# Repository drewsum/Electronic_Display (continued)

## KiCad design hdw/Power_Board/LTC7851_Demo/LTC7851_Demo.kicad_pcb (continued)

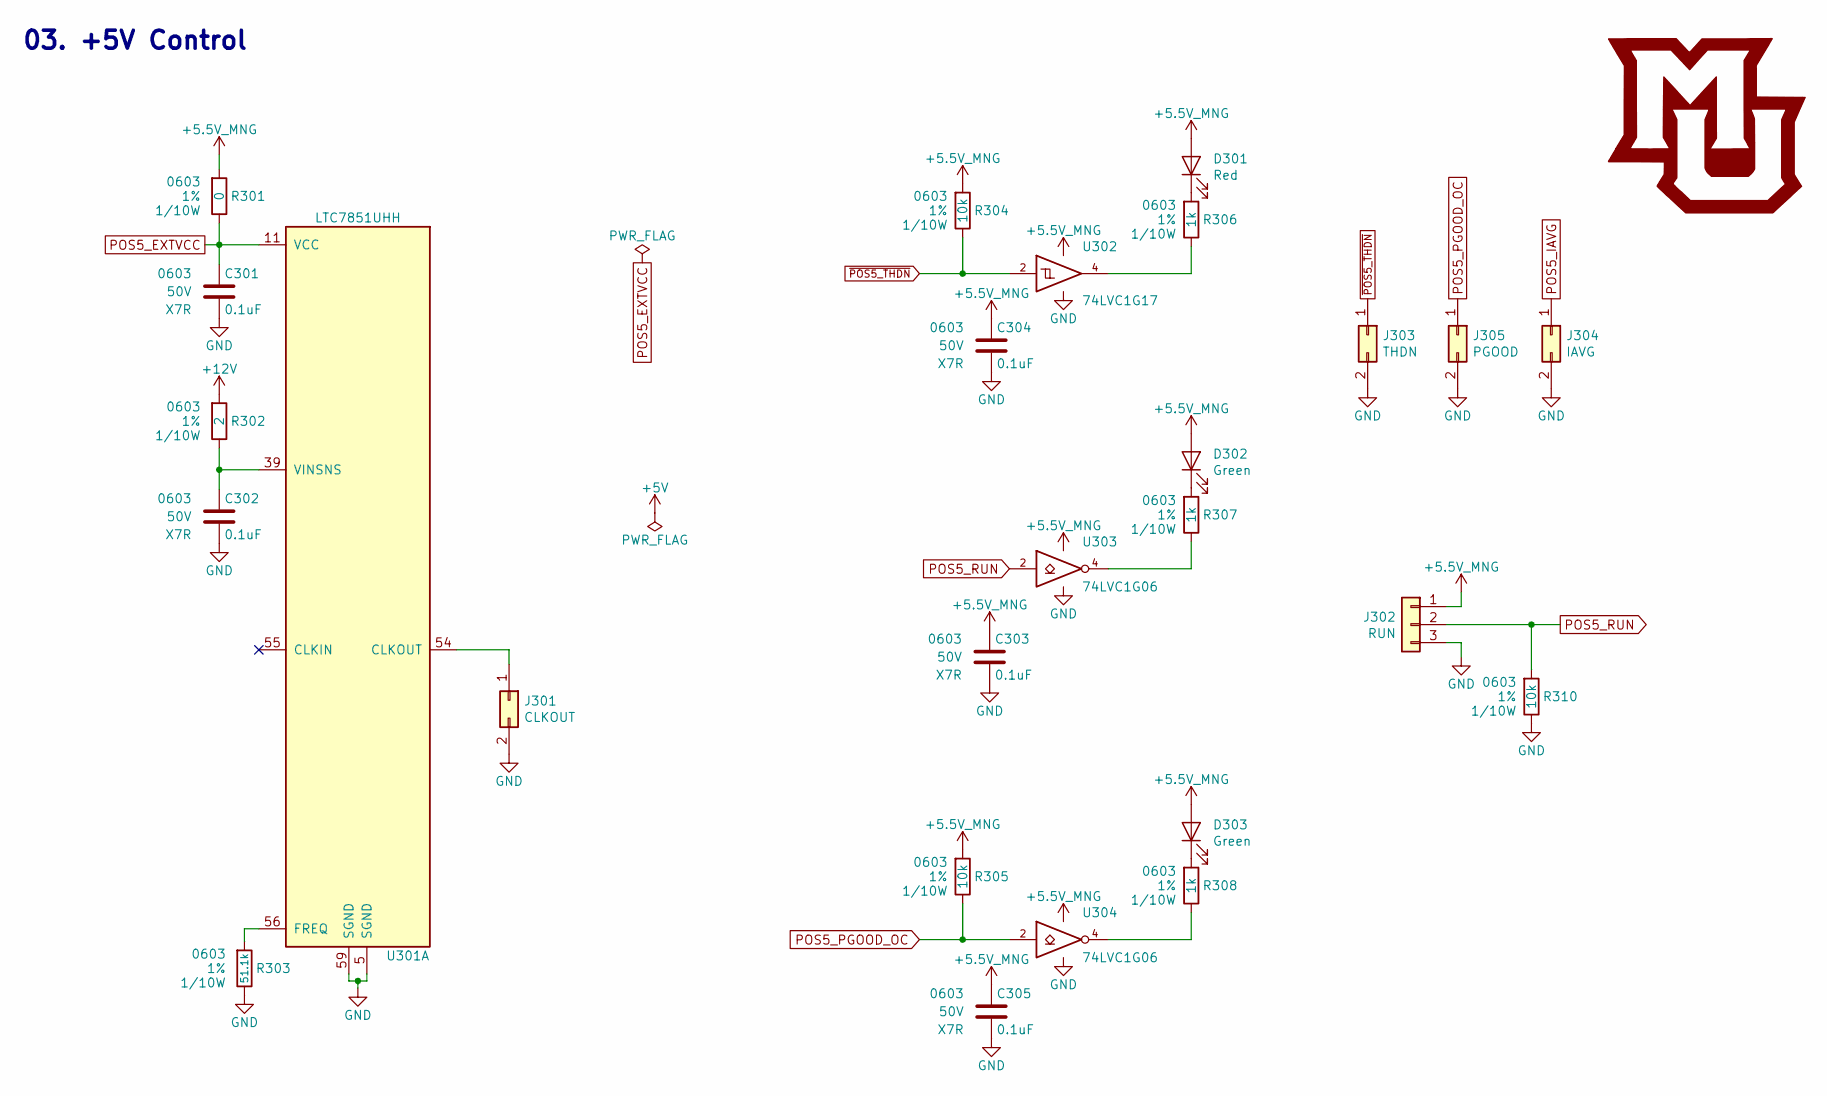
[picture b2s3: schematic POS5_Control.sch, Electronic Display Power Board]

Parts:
C301, C302, C303, C304, C305: 0.1uF; C_0603; Voltage 50V; Digi-Key PN 490-4779-1-ND
D301: Red; LED_0603; Digi-Key PN 160-1447-1-ND
D302, D303: Green; LED_0603; Digi-Key PN 160-1446-1-ND
J301: CLKOUT; Pin_Header_Straight_1x02_Pitch2.54mm
J302: RUN; Pin_Header_Straight_1x03_Pitch2.54mm
J303: THDN; Pin_Header_Straight_1x02_Pitch2.54mm
J304: IAVG; Pin_Header_Straight_1x02_Pitch2.54mm
J305: PGOOD; Pin_Header_Straight_1x02_Pitch2.54mm
R301: 0; R_0603; Tolerance 1%; Digi-Key PN 311-0.0GRCT-ND
R302: 2; R_0603; Tolerance 1%; Digi-Key PN RMCF0603FT2R00CT-ND
R303: 51.1k; R_0603; Tolerance 1%; Digi-Key PN P51.1KHCT-ND
R304, R305, R310: 10k; R_0603; Tolerance 1%; Digi-Key PN RHM10KADCT-ND
R306, R307, R308: 1k; R_0603; Tolerance 1%; Digi-Key PN RHM1.0KDCT-ND
U301: LTC7851UHH; QFN-58-1EP_9x5mm_Pitch0.4mm; Digi-Key PN LTC7851IUHH#PBF-ND
U302: 74LVC1G17; SOT-353_SC-70-5; Digi-Key PN 296-11934-1-ND
U303, U304: 74LVC1G06; SOT-353_SC-70-5; Digi-Key PN 296-8484-1-ND

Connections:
+5.5V_MNG: C303.1, C304.1, C305.1, D301.2 (A), D302.2 (A), D303.2 (A), J302.1, R301.1, R304.1, R305.1, U302.5 (VCC), U303.5 (VCC), U304.5 (VCC); also elsewhere on the board
+12V: R302.1; also elsewhere on the board
GND: C301.2, C302.2, C303.2, C304.2, C305.2, J301.2, J302.3, J303.2, J304.2, J305.2, R303.2, R310.2, U301.5 (SGND), U301.59 (SGND), U302.3 (GND), U303.3 (GND), U304.3 (GND); also elsewhere on the board
unnamed: C302.1, R302.2, U301.39 (VINSNS)
unnamed: D301.1 (K), R306.1
unnamed: D302.1 (K), R307.1
unnamed: D303.1 (K), R308.1
unnamed: J301.1, U301.54 (CLKOUT)
unnamed: R303.1, U301.56 (FREQ)
unnamed: R306.2, U302.4
unnamed: R307.2, U303.4
unnamed: R308.2, U304.4
POS5_EXTVCC: C301.1, R301.2, U301.11 (VCC); also elsewhere on the board
POS5_IAVG: J304.1; also elsewhere on the board
POS5_PGOOD_OC: J305.1, R305.2, U304.2; also elsewhere on the board
POS5_RUN: J302.2, R310.1, U303.2; also elsewhere on the board
~POS5_THDN: J303.1, R304.2, U302.2; also elsewhere on the board

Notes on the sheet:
03. +5V Control

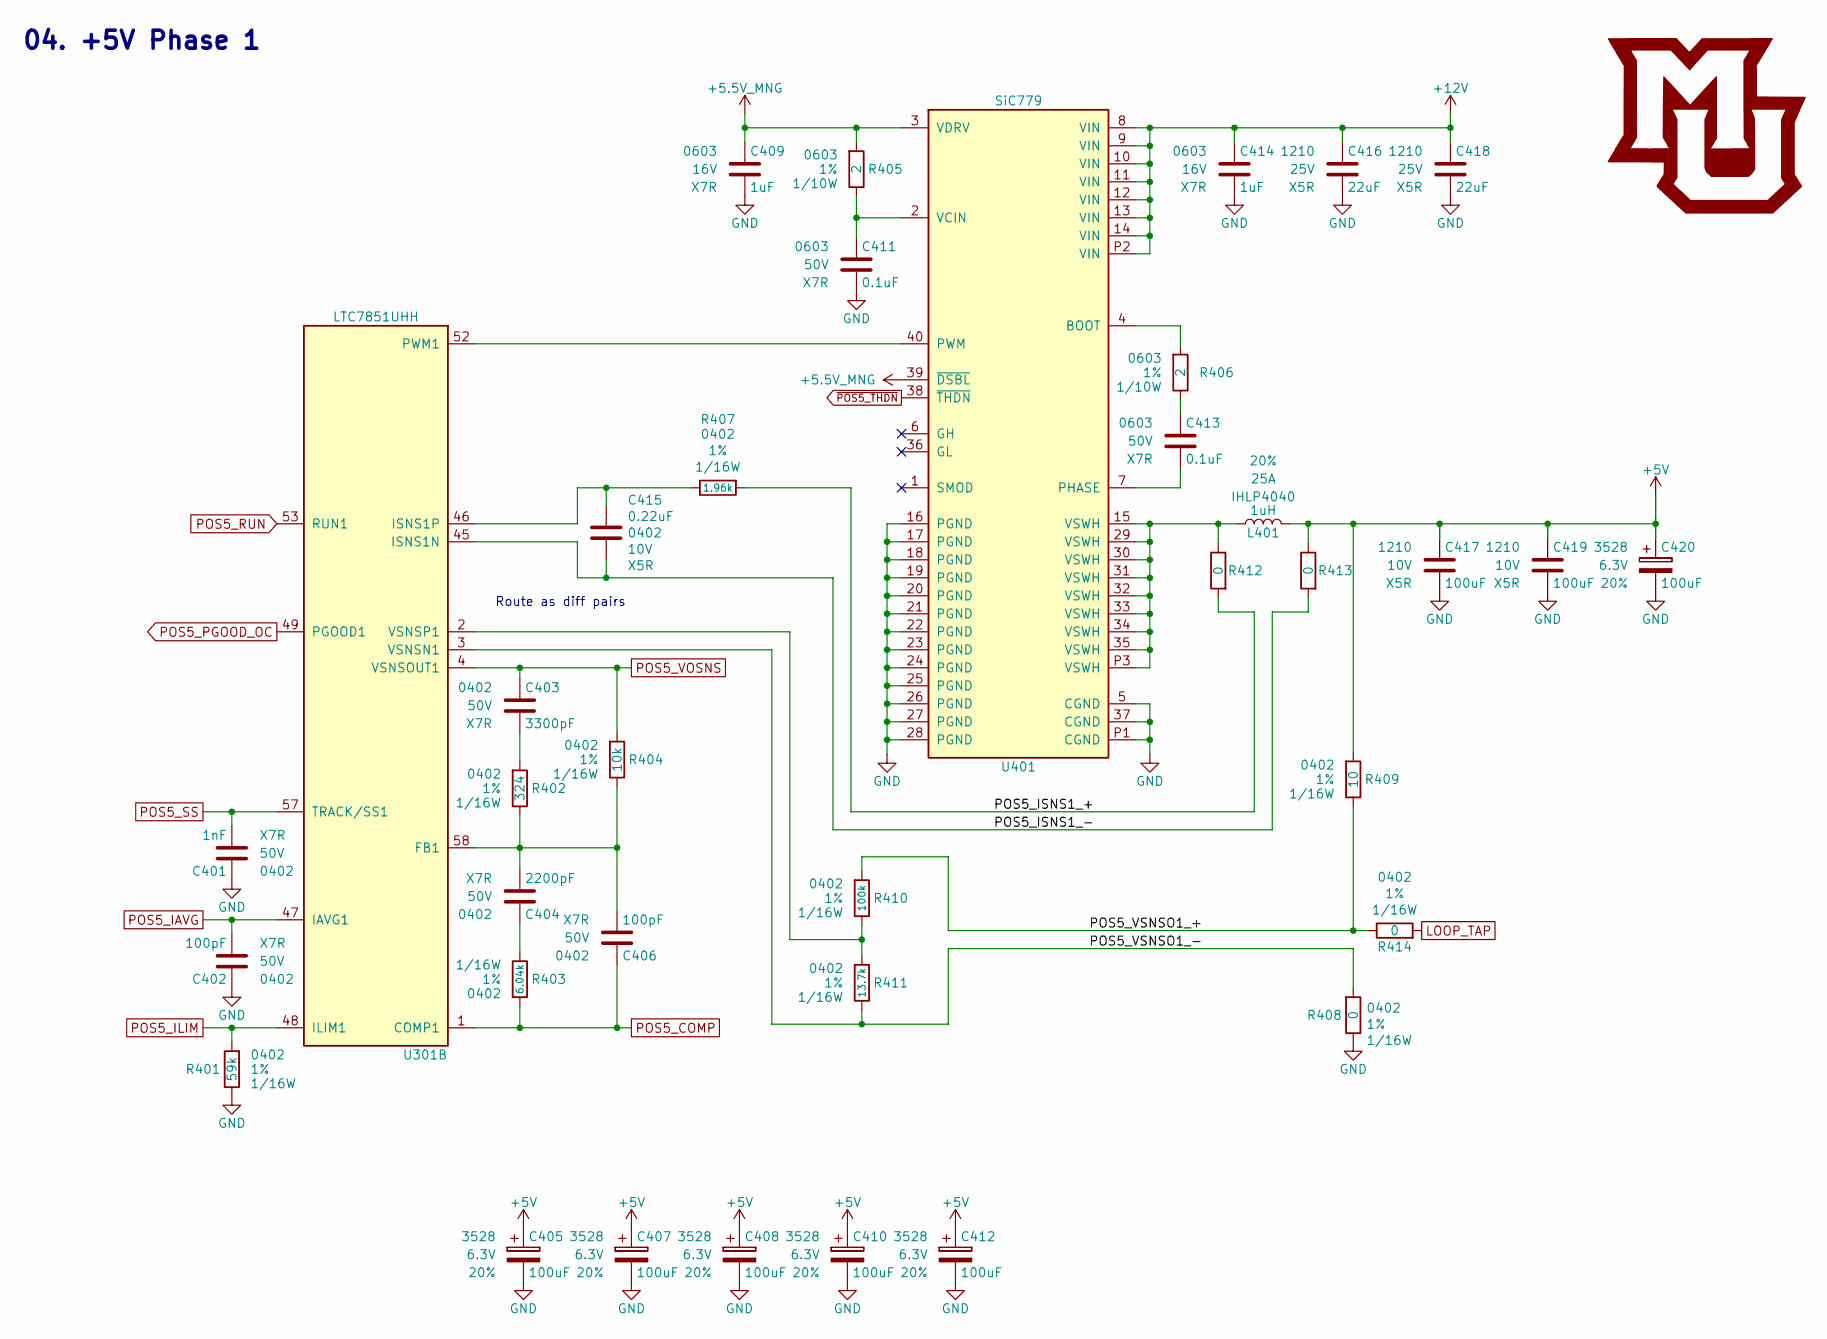
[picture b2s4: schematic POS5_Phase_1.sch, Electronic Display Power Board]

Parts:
C401: 1nF; C_0402; Voltage 50V; Digi-Key PN 311-1080-1-ND
C402, C406: 100pF; C_0402; Voltage 50V; Digi-Key PN 478-1089-1-ND
C403: 3300pF; C_0402; Voltage 50V; Digi-Key PN 478-5132-1-ND
C404: 2200pF; C_0402; Voltage 50V; Digi-Key PN 478-1105-1-ND
C405, C407, C408, C410, C412, C420: 100uF; CP_Tantalum_Case-B_EIA-3528-21_Reflow; Voltage 6.3V; Tolerance 20%; Digi-Key PN 478-9994-1-ND
C409, C414: 1uF; C_0603; Voltage 16V; Digi-Key PN 1276-6524-1-ND
C411, C413: 0.1uF; C_0603; Voltage 50V; Digi-Key PN 490-4779-1-ND
C415: 0.22uF; C_0402; Voltage 10V; Digi-Key PN 1276-1049-1-ND
C416, C418: 22uF; C_1210; Voltage 25V; Digi-Key PN 445-1436-1-ND
C417, C419: 100uF; C_1210; Voltage 10V; Digi-Key PN 587-3432-1-ND
L401: 1uH; L_Vishay_IHLP-4040; Tolerance 20%; Digi-Key PN 541-1306-1-ND
R401: 59k; R_0402; Tolerance 1%; Digi-Key PN P59KDCCT-ND
R402: 324; R_0402; Tolerance 1%; Digi-Key PN YAG3118CT-ND
R403: 6.04k; R_0402; Tolerance 1%; Digi-Key PN RMCF0402FT6K04CT-ND
R404: 10k; R_0402; Tolerance 1%; Digi-Key PN 311-10.0KLRCT-ND
R405, R406: 2; R_0603; Tolerance 1%; Digi-Key PN RMCF0603FT2R00CT-ND
R407: 1.96k; R_0402; Tolerance 1%; Digi-Key PN 311-1.96KLRCT-ND
R408, R412, R413, R414: 0; R_0402; Tolerance 1%; Digi-Key PN RMCF0402ZT0R00CT-ND
R409: 10; R_0402; Tolerance 1%; Digi-Key PN 311-10.0LRCT-ND
R410: 100k; R_0402; Tolerance 1%; Digi-Key PN 311-100KLRCT-ND
R411: 13.7k; R_0402; Tolerance 1%; Digi-Key PN 311-13.7KLRCT-ND
U301: LTC7851UHH; QFN-58-1EP_9x5mm_Pitch0.4mm; Digi-Key PN LTC7851IUHH#PBF-ND
U401: SiC779; MLP66-40_6x6mm_Pitch0.5mm; Digi-Key PN SIC779CD-T1-GE3CT-ND

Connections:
+5.5V_MNG: C409.1, R405.1, U401.3 (VDRV), U401.39 (~DSBL); also elsewhere on the board
+5V: C405.1, C407.1, C408.1, C410.1, C412.1, C417.1, C419.1, C420.1, L401.2, R409.1, R413.2; also elsewhere on the board
+12V: C414.1, C416.1, C418.1, U401.8 (VIN), U401.9 (VIN), U401.10 (VIN), U401.11 (VIN), U401.12 (VIN), U401.13 (VIN), U401.14 (VIN), U401.P2 (VIN); also elsewhere on the board
/POS5 Phase 1/POS5_ISNS1_+: R407.1, R412.1
/POS5 Phase 1/POS5_ISNS1_-: C415.1, R413.1, U301.45 (ISNS1N)
/POS5 Phase 1/POS5_VSNSO1_+: R409.2, R410.1, R414.2
/POS5 Phase 1/POS5_VSNSO1_-: R408.1, R411.2, U301.3 (VSNSN1)
GND: C401.1, C402.1, C405.2, C407.2, C408.2, C409.2, C410.2, C411.2, C412.2, C414.2, C416.2, C417.2, C418.2, C419.2, C420.2, R401.2, R408.2, U401.5 (CGND), U401.16 (PGND), U401.17 (PGND), U401.18 (PGND), U401.19 (PGND), U401.20 (PGND), U401.21 (PGND), U401.22 (PGND), U401.23 (PGND), U401.24 (PGND), U401.25 (PGND), U401.26 (PGND), U401.27 (PGND), U401.28 (PGND), U401.37 (CGND), U401.P1 (CGND); also elsewhere on the board
LOOP_TAP: R414.1; also elsewhere on the board
unnamed: C403.2, R402.1
unnamed: C404.1, R403.2
unnamed: C404.2, C406.2, R402.2, R404.2, U301.58 (FB1)
unnamed: C411.1, R405.2, U401.2 (VCIN)
unnamed: C413.1, R406.2
unnamed: C413.2, U401.7 (PHASE)
unnamed: C415.2, R407.2, U301.46 (ISNS1P)
unnamed: L401.1, R412.2, U401.15 (VSWH), U401.29 (VSWH), U401.30 (VSWH), U401.31 (VSWH), U401.32 (VSWH), U401.33 (VSWH), U401.34 (VSWH), U401.35 (VSWH), U401.P3 (VSWH)
unnamed: R406.1, U401.4 (BOOT)
unnamed: R410.2, R411.1, U301.2 (VSNSP1)
unnamed: U301.52 (PWM1), U401.40 (PWM)
POS5_COMP: C406.1, R403.1, U301.1 (COMP1); also elsewhere on the board
POS5_IAVG: C402.2, U301.47 (IAVG1); also elsewhere on the board
POS5_ILIM: R401.1, U301.48 (ILIM1); also elsewhere on the board
POS5_PGOOD_OC: U301.49 (PGOOD1); also elsewhere on the board
POS5_RUN: U301.53 (RUN1); also elsewhere on the board
POS5_SS: C401.2, U301.57 (TRACK/SS1); also elsewhere on the board
POS5_VOSNS: C403.1, R404.1, U301.4 (VSNSOUT1); also elsewhere on the board
~POS5_THDN: U401.38 (~THDN); also elsewhere on the board

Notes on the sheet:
Route as diff pairs
04. +5V Phase 1

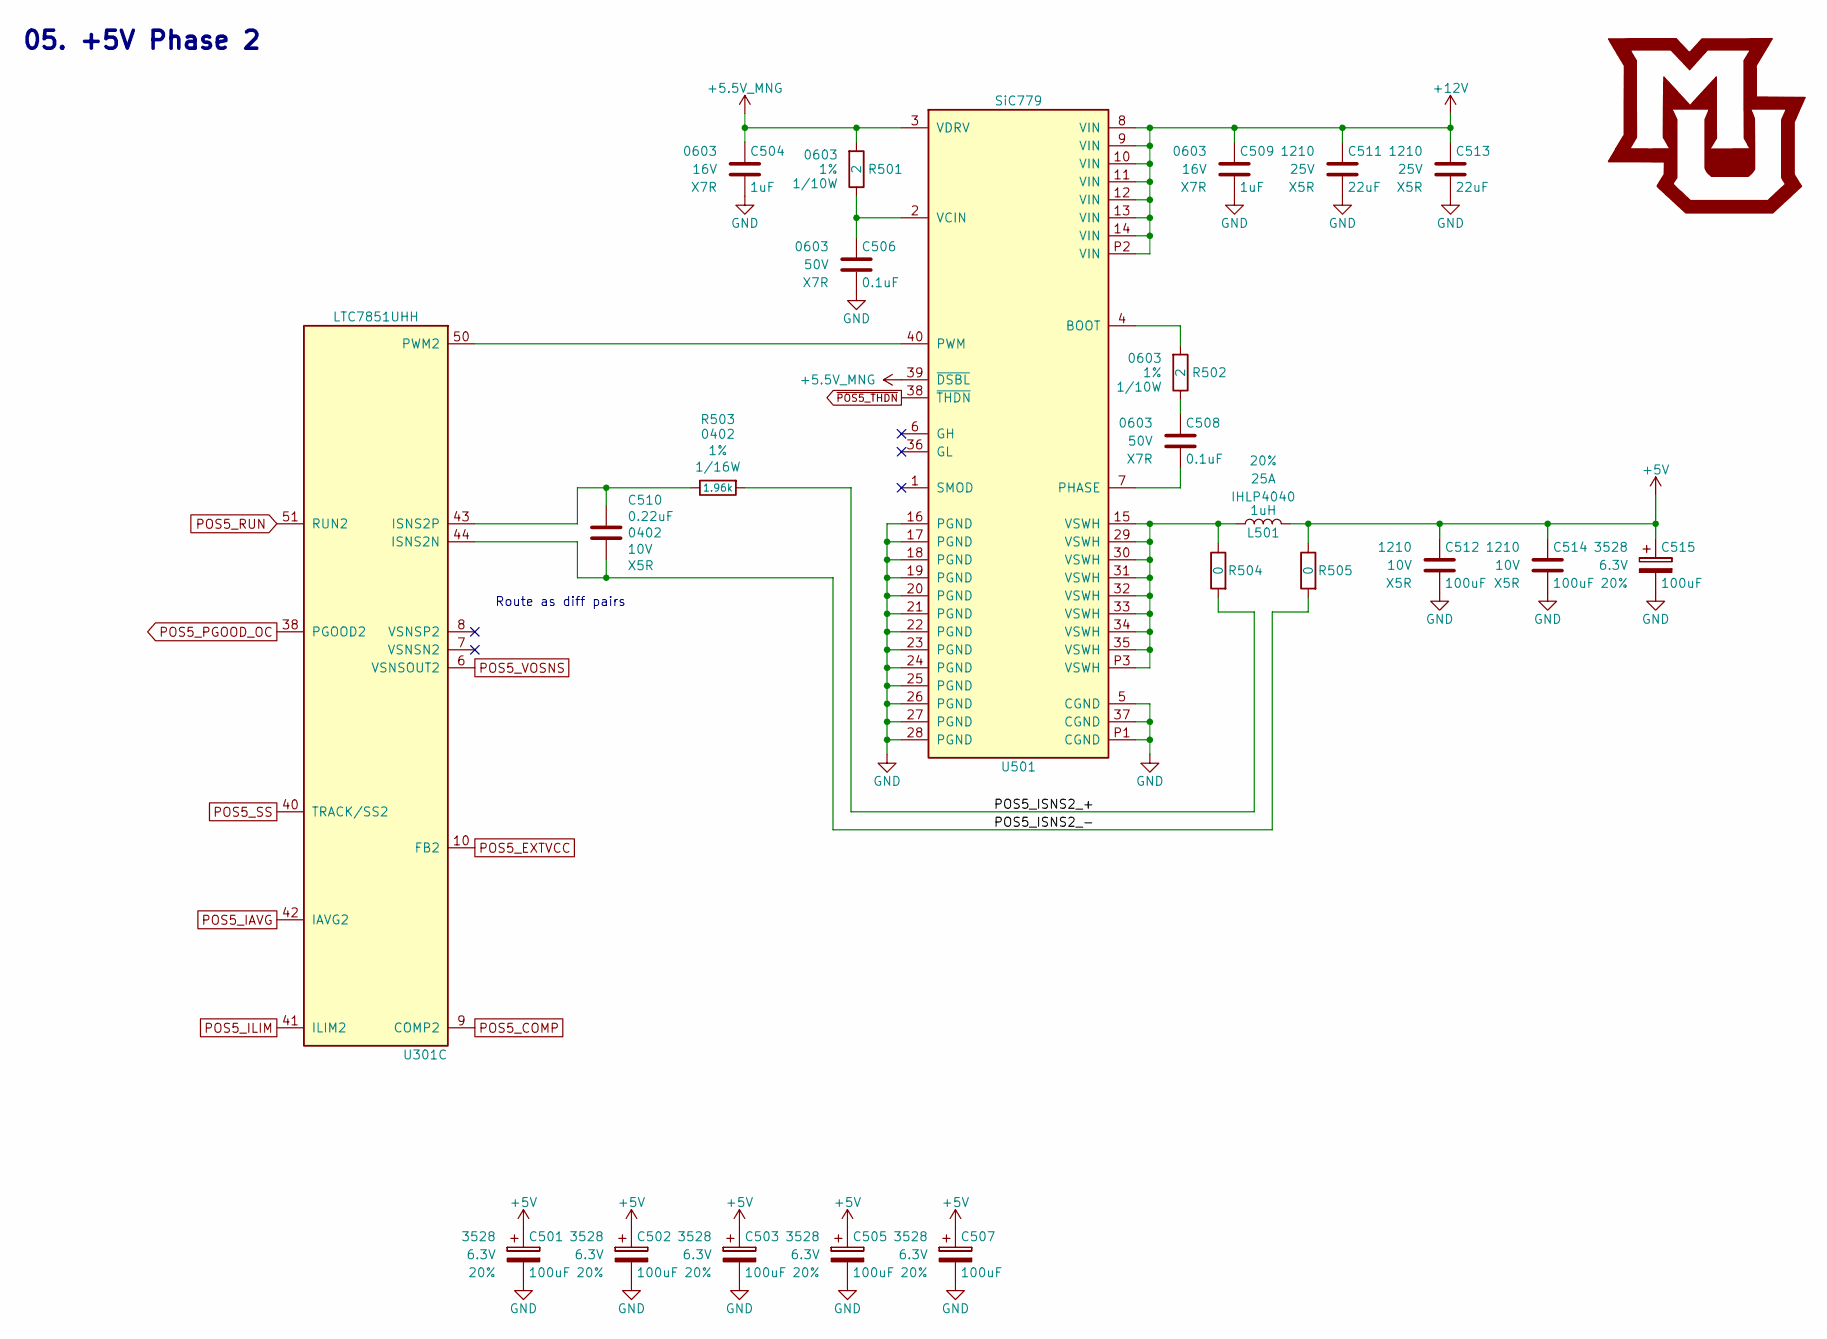
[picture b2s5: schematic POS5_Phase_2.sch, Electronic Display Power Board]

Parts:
C501, C502, C503, C505, C507, C515: 100uF; CP_Tantalum_Case-B_EIA-3528-21_Reflow; Voltage 6.3V; Tolerance 20%; Digi-Key PN 478-9994-1-ND
C504: 1uF; C_0603_HandSoldering; Voltage 16V; Digi-Key PN 1276-6524-1-ND
C506, C508: 0.1uF; C_0603; Voltage 50V; Digi-Key PN 490-4779-1-ND
C509: 1uF; C_0603; Voltage 16V; Digi-Key PN 1276-6524-1-ND
C510: 0.22uF; C_0402; Voltage 10V; Digi-Key PN 1276-1049-1-ND
C511, C513: 22uF; C_1210; Voltage 25V; Digi-Key PN 445-1436-1-ND
C512, C514: 100uF; C_1210; Voltage 10V; Digi-Key PN 587-3432-1-ND
L501: 1uH; L_Vishay_IHLP-4040; Tolerance 20%; Digi-Key PN 541-1306-1-ND
R501, R502: 2; R_0603; Tolerance 1%; Digi-Key PN RMCF0603FT2R00CT-ND
R503: 1.96k; R_0402; Tolerance 1%; Digi-Key PN 311-1.96KLRCT-ND
R504, R505: 0; R_0402; Tolerance 1%; Digi-Key PN RMCF0402ZT0R00CT-ND
U301: LTC7851UHH; QFN-58-1EP_9x5mm_Pitch0.4mm; Digi-Key PN LTC7851IUHH#PBF-ND
U501: SiC779; MLP66-40_6x6mm_Pitch0.5mm; Digi-Key PN SIC779CD-T1-GE3CT-ND

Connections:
+5.5V_MNG: C504.1, R501.1, U501.3 (VDRV), U501.39 (~DSBL); also elsewhere on the board
+5V: C501.1, C502.1, C503.1, C505.1, C507.1, C512.1, C514.1, C515.1, L501.2, R505.2; also elsewhere on the board
+12V: C509.1, C511.1, C513.1, U501.8 (VIN), U501.9 (VIN), U501.10 (VIN), U501.11 (VIN), U501.12 (VIN), U501.13 (VIN), U501.14 (VIN), U501.P2 (VIN); also elsewhere on the board
/POS5 Phase 2/POS5_ISNS2_+: R503.1, R504.1
/POS5 Phase 2/POS5_ISNS2_-: C510.1, R505.1, U301.44 (ISNS2N)
GND: C501.2, C502.2, C503.2, C504.2, C505.2, C506.2, C507.2, C509.2, C511.2, C512.2, C513.2, C514.2, C515.2, U501.5 (CGND), U501.16 (PGND), U501.17 (PGND), U501.18 (PGND), U501.19 (PGND), U501.20 (PGND), U501.21 (PGND), U501.22 (PGND), U501.23 (PGND), U501.24 (PGND), U501.25 (PGND), U501.26 (PGND), U501.27 (PGND), U501.28 (PGND), U501.37 (CGND), U501.P1 (CGND); also elsewhere on the board
unnamed: C506.1, R501.2, U501.2 (VCIN)
unnamed: C508.1, R502.2
unnamed: C508.2, U501.7 (PHASE)
unnamed: C510.2, R503.2, U301.43 (ISNS2P)
unnamed: L501.1, R504.2, U501.15 (VSWH), U501.29 (VSWH), U501.30 (VSWH), U501.31 (VSWH), U501.32 (VSWH), U501.33 (VSWH), U501.34 (VSWH), U501.35 (VSWH), U501.P3 (VSWH)
unnamed: R502.1, U501.4 (BOOT)
unnamed: U301.50 (PWM2), U501.40 (PWM)
POS5_COMP: U301.9 (COMP2); also elsewhere on the board
POS5_EXTVCC: U301.10 (FB2); also elsewhere on the board
POS5_IAVG: U301.42 (IAVG2); also elsewhere on the board
POS5_ILIM: U301.41 (ILIM2); also elsewhere on the board
POS5_PGOOD_OC: U301.38 (PGOOD2); also elsewhere on the board
POS5_RUN: U301.51 (RUN2); also elsewhere on the board
POS5_SS: U301.40 (TRACK/SS2); also elsewhere on the board
POS5_VOSNS: U301.6 (VSNSOUT2); also elsewhere on the board
~POS5_THDN: U501.38 (~THDN); also elsewhere on the board

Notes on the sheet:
05. +5V Phase 2
Route as diff pairs

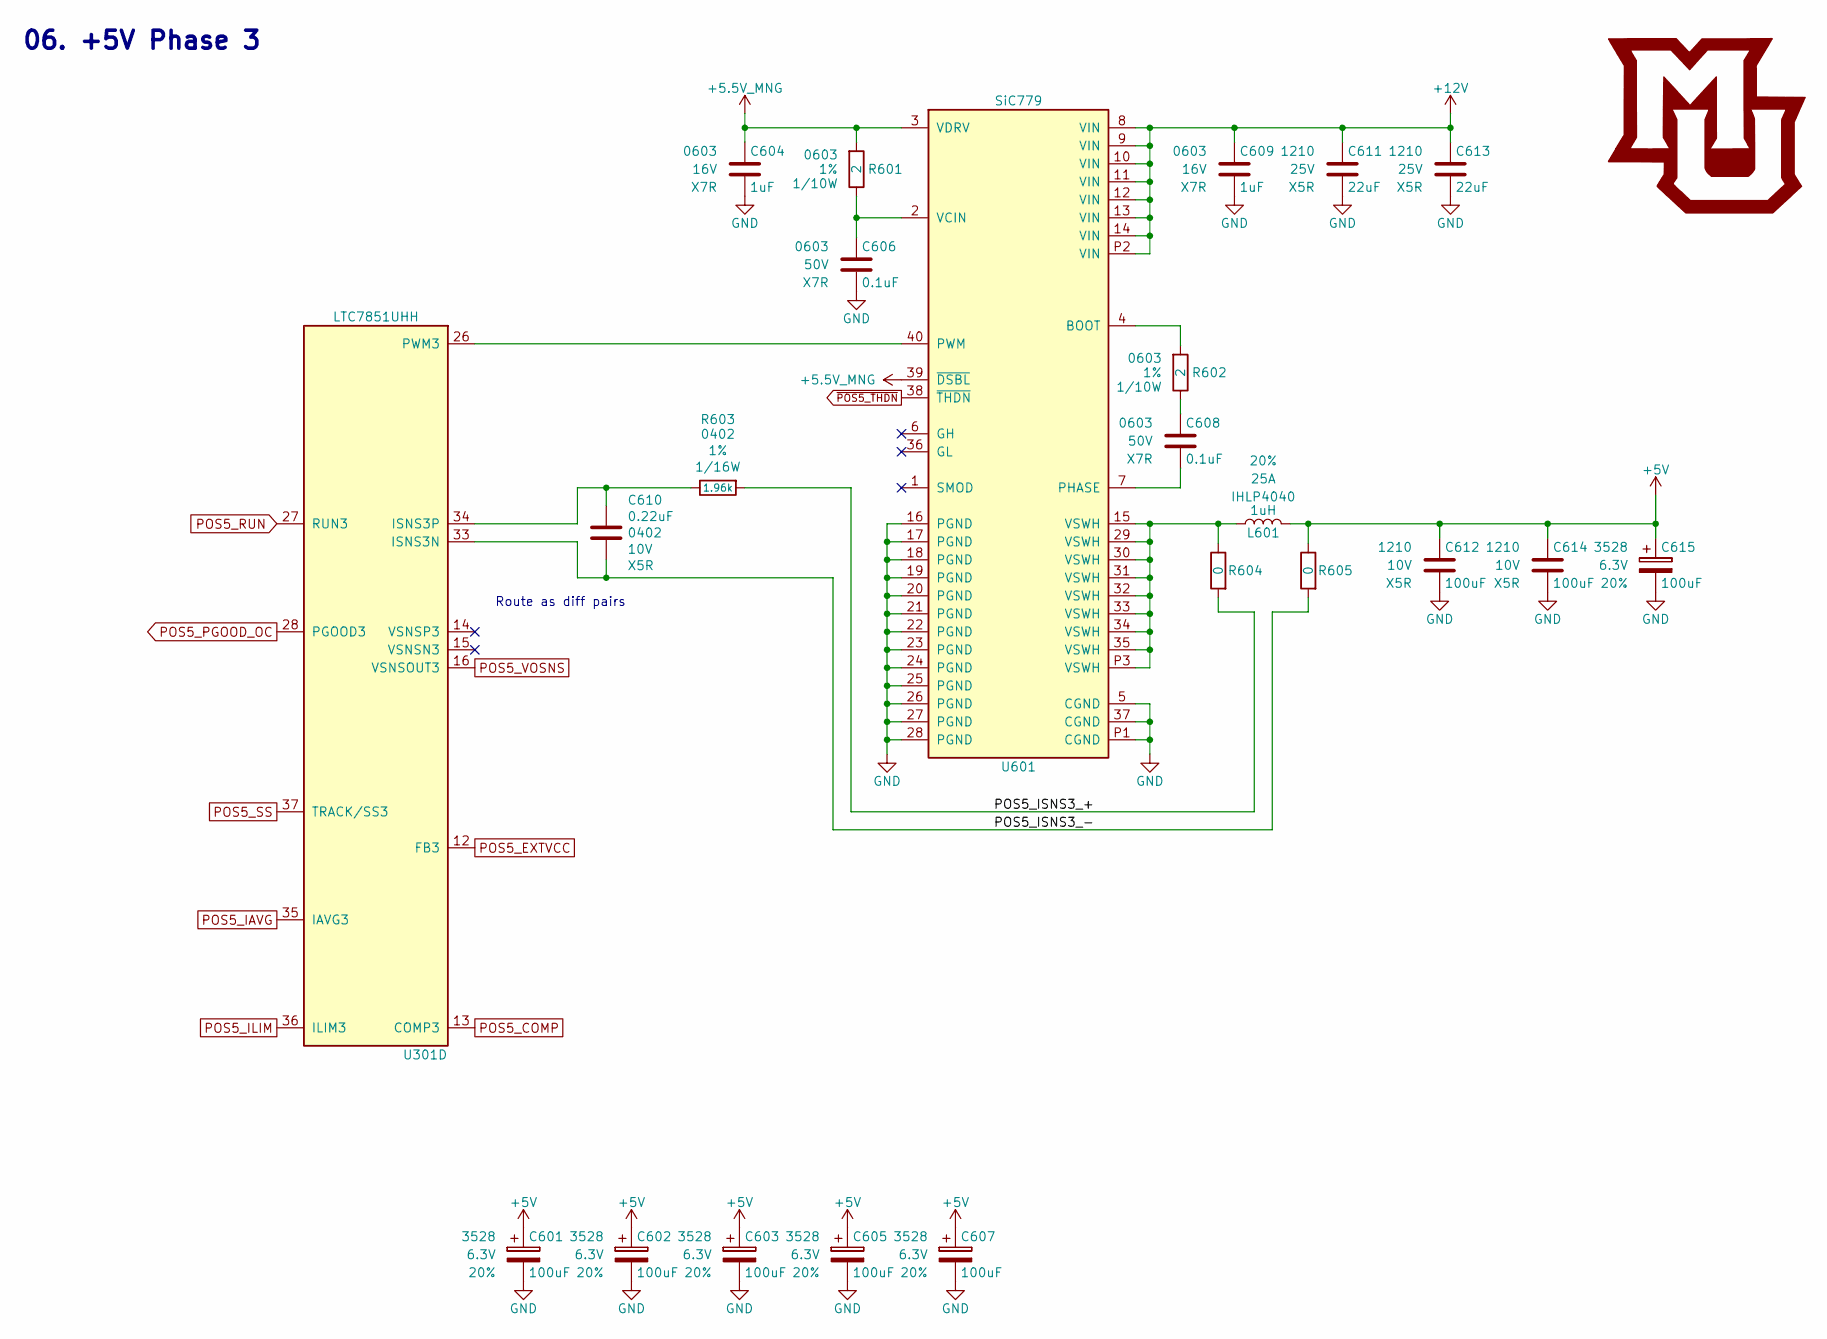
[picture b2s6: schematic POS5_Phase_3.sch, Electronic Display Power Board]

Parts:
C601, C602, C603, C605, C607, C615: 100uF; CP_Tantalum_Case-B_EIA-3528-21_Reflow; Voltage 6.3V; Tolerance 20%; Digi-Key PN 478-9994-1-ND
C604, C609: 1uF; C_0603; Voltage 16V; Digi-Key PN 1276-6524-1-ND
C606, C608: 0.1uF; C_0603; Voltage 50V; Digi-Key PN 490-4779-1-ND
C610: 0.22uF; C_0402; Voltage 10V; Digi-Key PN 1276-1049-1-ND
C611, C613: 22uF; C_1210; Voltage 25V; Digi-Key PN 445-1436-1-ND
C612, C614: 100uF; C_1210; Voltage 10V; Digi-Key PN 587-3432-1-ND
L601: 1uH; L_Vishay_IHLP-4040; Tolerance 20%; Digi-Key PN 541-1306-1-ND
R601, R602: 2; R_0603; Tolerance 1%; Digi-Key PN RMCF0603FT2R00CT-ND
R603: 1.96k; R_0402; Tolerance 1%; Digi-Key PN 311-1.96KLRCT-ND
R604, R605: 0; R_0402; Tolerance 1%; Digi-Key PN RMCF0402ZT0R00CT-ND
U301: LTC7851UHH; QFN-58-1EP_9x5mm_Pitch0.4mm; Digi-Key PN LTC7851IUHH#PBF-ND
U601: SiC779; MLP66-40_6x6mm_Pitch0.5mm; Digi-Key PN SIC779CD-T1-GE3CT-ND

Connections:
+5.5V_MNG: C604.1, R601.1, U601.3 (VDRV), U601.39 (~DSBL); also elsewhere on the board
+5V: C601.1, C602.1, C603.1, C605.1, C607.1, C612.1, C614.1, C615.1, L601.2, R605.2; also elsewhere on the board
+12V: C609.1, C611.1, C613.1, U601.8 (VIN), U601.9 (VIN), U601.10 (VIN), U601.11 (VIN), U601.12 (VIN), U601.13 (VIN), U601.14 (VIN), U601.P2 (VIN); also elsewhere on the board
/POS5 Phase 3/POS5_ISNS3_+: R603.1, R604.1
/POS5 Phase 3/POS5_ISNS3_-: C610.1, R605.1, U301.33 (ISNS3N)
GND: C601.2, C602.2, C603.2, C604.2, C605.2, C606.2, C607.2, C609.2, C611.2, C612.2, C613.2, C614.2, C615.2, U601.5 (CGND), U601.16 (PGND), U601.17 (PGND), U601.18 (PGND), U601.19 (PGND), U601.20 (PGND), U601.21 (PGND), U601.22 (PGND), U601.23 (PGND), U601.24 (PGND), U601.25 (PGND), U601.26 (PGND), U601.27 (PGND), U601.28 (PGND), U601.37 (CGND), U601.P1 (CGND); also elsewhere on the board
unnamed: C606.1, R601.2, U601.2 (VCIN)
unnamed: C608.1, R602.2
unnamed: C608.2, U601.7 (PHASE)
unnamed: C610.2, R603.2, U301.34 (ISNS3P)
unnamed: L601.1, R604.2, U601.15 (VSWH), U601.29 (VSWH), U601.30 (VSWH), U601.31 (VSWH), U601.32 (VSWH), U601.33 (VSWH), U601.34 (VSWH), U601.35 (VSWH), U601.P3 (VSWH)
unnamed: R602.1, U601.4 (BOOT)
unnamed: U301.26 (PWM3), U601.40 (PWM)
POS5_COMP: U301.13 (COMP3); also elsewhere on the board
POS5_EXTVCC: U301.12 (FB3); also elsewhere on the board
POS5_IAVG: U301.35 (IAVG3); also elsewhere on the board
POS5_ILIM: U301.36 (ILIM3); also elsewhere on the board
POS5_PGOOD_OC: U301.28 (PGOOD3); also elsewhere on the board
POS5_RUN: U301.27 (RUN3); also elsewhere on the board
POS5_SS: U301.37 (TRACK/SS3); also elsewhere on the board
POS5_VOSNS: U301.16 (VSNSOUT3); also elsewhere on the board
~POS5_THDN: U601.38 (~THDN); also elsewhere on the board

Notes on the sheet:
06. +5V Phase 3
Route as diff pairs

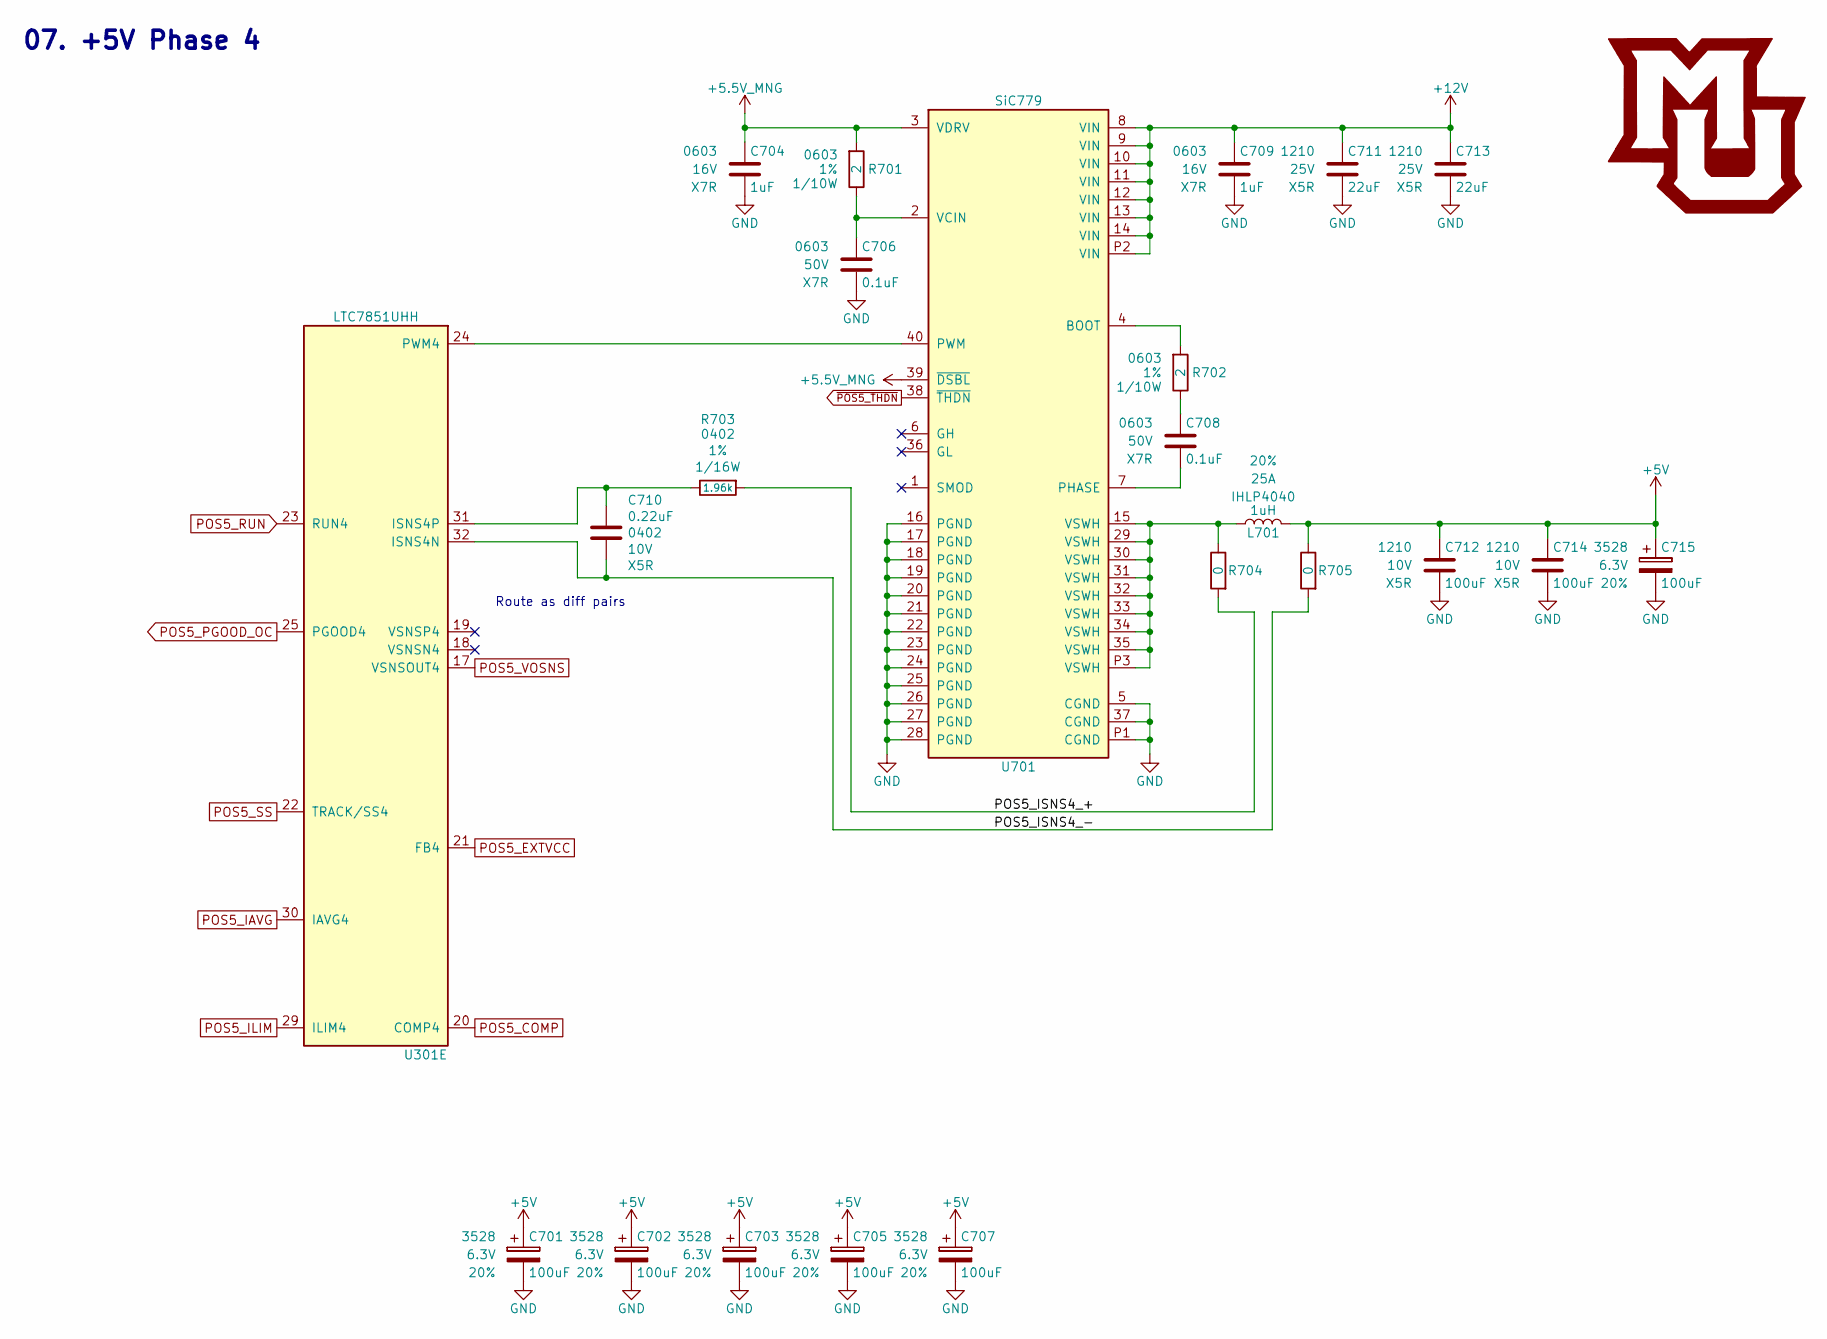
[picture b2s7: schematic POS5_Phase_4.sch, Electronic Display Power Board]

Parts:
C701, C702, C703, C705, C707, C715: 100uF; CP_Tantalum_Case-B_EIA-3528-21_Reflow; Voltage 6.3V; Tolerance 20%; Digi-Key PN 478-9994-1-ND
C704, C709: 1uF; C_0603; Voltage 16V; Digi-Key PN 1276-6524-1-ND
C706, C708: 0.1uF; C_0603; Voltage 50V; Digi-Key PN 490-4779-1-ND
C710: 0.22uF; C_0402; Voltage 10V; Digi-Key PN 1276-1049-1-ND
C711, C713: 22uF; C_1210; Voltage 25V; Digi-Key PN 445-1436-1-ND
C712, C714: 100uF; C_1210; Voltage 10V; Digi-Key PN 587-3432-1-ND
L701: 1uH; L_Vishay_IHLP-4040; Tolerance 20%; Digi-Key PN 541-1306-1-ND
R701, R702: 2; R_0603; Tolerance 1%; Digi-Key PN RMCF0603FT2R00CT-ND
R703: 1.96k; R_0402; Tolerance 1%; Digi-Key PN 311-1.96KLRCT-ND
R704, R705: 0; R_0402; Tolerance 1%; Digi-Key PN RMCF0402ZT0R00CT-ND
U301: LTC7851UHH; QFN-58-1EP_9x5mm_Pitch0.4mm; Digi-Key PN LTC7851IUHH#PBF-ND
U701: SiC779; MLP66-40_6x6mm_Pitch0.5mm; Digi-Key PN SIC779CD-T1-GE3CT-ND

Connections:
+5.5V_MNG: C704.1, R701.1, U701.3 (VDRV), U701.39 (~DSBL); also elsewhere on the board
+5V: C701.1, C702.1, C703.1, C705.1, C707.1, C712.1, C714.1, C715.1, L701.2, R705.2; also elsewhere on the board
+12V: C709.1, C711.1, C713.1, U701.8 (VIN), U701.9 (VIN), U701.10 (VIN), U701.11 (VIN), U701.12 (VIN), U701.13 (VIN), U701.14 (VIN), U701.P2 (VIN); also elsewhere on the board
/POS5 Phase 4/POS5_ISNS4_+: R703.1, R704.1
/POS5 Phase 4/POS5_ISNS4_-: C710.1, R705.1, U301.32 (ISNS4N)
GND: C701.2, C702.2, C703.2, C704.2, C705.2, C706.2, C707.2, C709.2, C711.2, C712.2, C713.2, C714.2, C715.2, U701.5 (CGND), U701.16 (PGND), U701.17 (PGND), U701.18 (PGND), U701.19 (PGND), U701.20 (PGND), U701.21 (PGND), U701.22 (PGND), U701.23 (PGND), U701.24 (PGND), U701.25 (PGND), U701.26 (PGND), U701.27 (PGND), U701.28 (PGND), U701.37 (CGND), U701.P1 (CGND); also elsewhere on the board
unnamed: C706.1, R701.2, U701.2 (VCIN)
unnamed: C708.1, R702.2
unnamed: C708.2, U701.7 (PHASE)
unnamed: C710.2, R703.2, U301.31 (ISNS4P)
unnamed: L701.1, R704.2, U701.15 (VSWH), U701.29 (VSWH), U701.30 (VSWH), U701.31 (VSWH), U701.32 (VSWH), U701.33 (VSWH), U701.34 (VSWH), U701.35 (VSWH), U701.P3 (VSWH)
unnamed: R702.1, U701.4 (BOOT)
unnamed: U301.24 (PWM4), U701.40 (PWM)
POS5_COMP: U301.20 (COMP4); also elsewhere on the board
POS5_EXTVCC: U301.21 (FB4); also elsewhere on the board
POS5_IAVG: U301.30 (IAVG4); also elsewhere on the board
POS5_ILIM: U301.29 (ILIM4); also elsewhere on the board
POS5_PGOOD_OC: U301.25 (PGOOD4); also elsewhere on the board
POS5_RUN: U301.23 (RUN4); also elsewhere on the board
POS5_SS: U301.22 (TRACK/SS4); also elsewhere on the board
POS5_VOSNS: U301.17 (VSNSOUT4); also elsewhere on the board
~POS5_THDN: U701.38 (~THDN); also elsewhere on the board

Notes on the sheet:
07. +5V Phase 4
Route as diff pairs

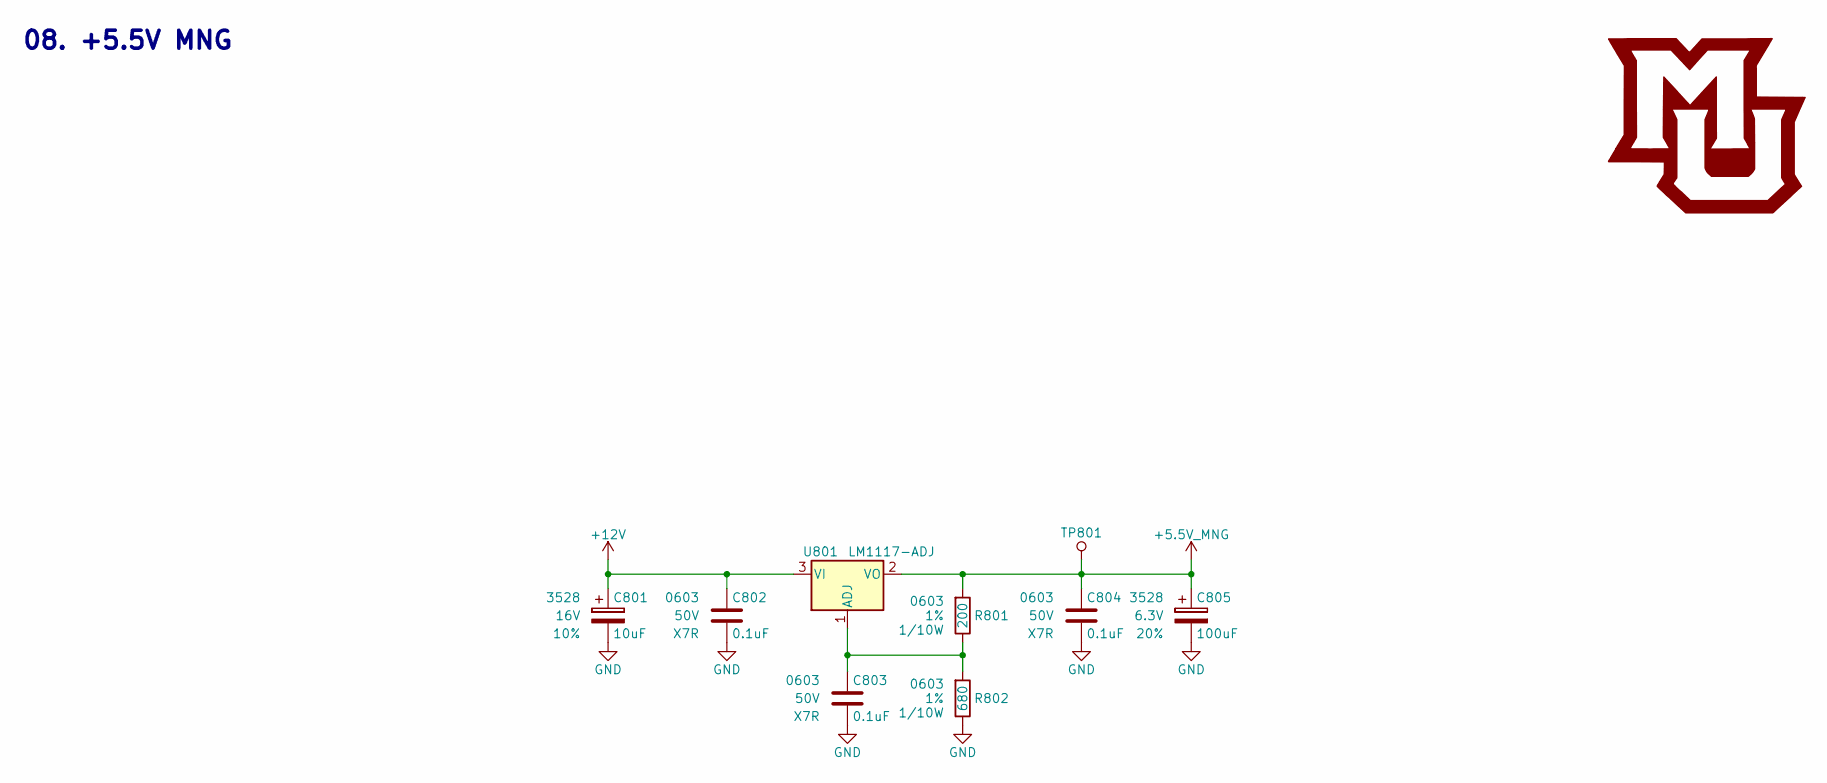
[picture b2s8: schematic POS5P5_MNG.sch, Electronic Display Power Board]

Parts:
C801: 10uF; CP_Tantalum_Case-B_EIA-3528-21_Reflow; Voltage 16V; Tolerance 10%; Digi-Key PN 399-5034-1-ND
C802, C803, C804: 0.1uF; C_0603; Voltage 50V; Digi-Key PN 490-4779-1-ND
C805: 100uF; CP_Tantalum_Case-B_EIA-3528-21_Reflow; Voltage 6.3V; Tolerance 20%; Digi-Key PN 478-9994-1-ND
R801: 200; R_0603; Tolerance 1%; Digi-Key PN MCT0603-200-CFCT-ND
R802: 680; R_0603; Tolerance 1%; Digi-Key PN P680HCT-ND
TP801: TP; Measurement_Point_Round-SMD-Pad_Small
U801: LM1117-ADJ; SOT-223-3_TabPin2; Digi-Key PN LM1117IMPX-ADJ/NOPBCT-ND

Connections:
+5.5V_MNG: C804.1, C805.1, R801.1, TP801.1, U801.2 (VO); also elsewhere on the board
+12V: C801.1, C802.1, U801.3 (VI); also elsewhere on the board
GND: C801.2, C802.2, C803.2, C804.2, C805.2, R802.2; also elsewhere on the board
unnamed: C803.1, R801.2, R802.1, U801.1 (ADJ)

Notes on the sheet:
08. +5.5V MNG

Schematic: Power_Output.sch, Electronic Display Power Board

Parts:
J901, J902: +5V OUT; Wuerth_7461096_M4_Shank_9pos; Digi-Key PN 732-3214-ND
J903, J904: GND OUT; Wuerth_7461096_M4_Shank_9pos; Digi-Key PN 732-3214-ND

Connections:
+5V: J901.1, J902.1; also elsewhere on the board
GND: J903.1, J904.1; also elsewhere on the board

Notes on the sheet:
Place bulk output caps close to terminals
09. Power Output

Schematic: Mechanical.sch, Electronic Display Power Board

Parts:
MH1001, MH1003, MH1004, MH1006: MountingHole; MountingHole_3mm
MK1001, MK1002, MK1009, MK1010: 4-40 Screw; Digi-Key PN 36-9900-ND
MK1003, MK1004, MK1011, MK1012: 4-40 Standoff; Digi-Key PN 36-8400-ND

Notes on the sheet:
10. Mounting Holes and Mechanical Components
